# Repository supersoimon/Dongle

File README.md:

# Custom USB-C to MicroSD Dongle!
This is a custom USB Type C to MicroSD adapter capable of high-speed data transfer.

# Why I Made it :)
I've been struggling to find a USB-C to MicroSD for a Bambu Labs A1 at my school, and so I haven't been able to print on it. I found that it could be a cool project on PCB design, and a way to support my school's 3D-printing program!

# Parts
It uses a 105444 Molex USB-C plug and a 104031-0811 Molex MicroSD receptacle, connected by a GLK823 chip, with an onboard LED to show if data is transferring.

# CAD
The full CAD is available on Onshape here: https://cad.onshape.com/documents/0d5d8e7ff6d95221f6bb9616/w/a02504fd69371836af815b31/e/9594bd8276455d6ed6823f06?renderMode=0&uiState=6ab2c2f00285e009953060f3
Currently isn't going to have a case, I think it looks cooler raw.

# Images
 <br>
 <br>
 <br>
 <br>
 <br>

# BOM
| Item | Quantity | Cost (USD) | Notes |
| :--- | :---: | :---: | :--- |
| [PCB](https://cart.jlcpcb.com/shopcart/cart/) | 1 | $4.2 | |
| [PCB Shipping](https://cart.jlcpcb.com/shopcart/cart/) | 1 | $5.65 | |
| [GL823K](https://www.lcsc.com/product-detail/C284879.html) | 2 | $0.93 | |
| [Molex 105444](https://www.lcsc.com/product-detail/C134082.html) | 2 | $3.15 | |
| [Molex 104031-0811](https://www.lcsc.com/product-detail/C585350.html) | 2 | $1.67 | |
| [500mA resettable fuse](https://www.lcsc.com/product-detail/C2982262.html) | 5 | $0.39 | |
| [5.1k resistor 0805 package](https://www.lcsc.com/product-detail/C27834.html) | 100 | $0.6 | |
| [0 resistor 0805 package](https://www.lcsc.com/product-detail/C17477.html) | 100 | $0.45 | |
| [1k resistor 0805 package](https://www.lcsc.com/product-detail/C2907232.html) | 100 | $0.31 | |
| [red led 0805 package](https://www.lcsc.com/product-detail/C19171391.html) | 100 | $0.78 | |
| [0.1uF capacitor 0805 package](https://www.lcsc.com/product-detail/C49678.html) | 20 | $0.39 | |
| [1uF capacitor 0805 package](https://www.lcsc.com/product-detail/C28323.html) | 10 | $0.4 | |
| [4.7uF capacitor 0805 package](https://www.lcsc.com/product-detail/C1779.html) | 20 | $0.7 | |
| LCSC Shipping & Handling | 1 | $10.86 | |
| [Flux](https://www.amazon.ca/TOWOT-Soldering-Electronics-Pneumatic-Dispensing/dp/B0D8PRL5CP/) | 1 | $11.4 | Much of the cost is for me to start soldering these, as I've never done that before |
| [Solder Wire](https://amazon.ca/VIRALLOY®-Lead-Free-Solder-0-5mm-SAC0307/dp/B0FXX4GPWJ/) | 1 | $9.2 | |
| [ESD Tweezers](https://www.amazon.ca/Precision-ESD-Tweezers-Set-MMOBIEL/dp/B07N2QGS75/) | 1 | $7.14 | |
| [Solder Wick](https://www.amazon.ca/Solder-TOWOT-Desoldering-Wicks-SW-2530/dp/B0943PDCC4/) | 1 | $7.11 | |
| [99% IPA](https://www.amazon.ca/DELON-Isopropyl-Alcohol-Percent-Rubbing/dp/B0DD4HCV3S/) | 1 | $6.42 | |
| **Total** | **469** | **$71.75** | |fore",

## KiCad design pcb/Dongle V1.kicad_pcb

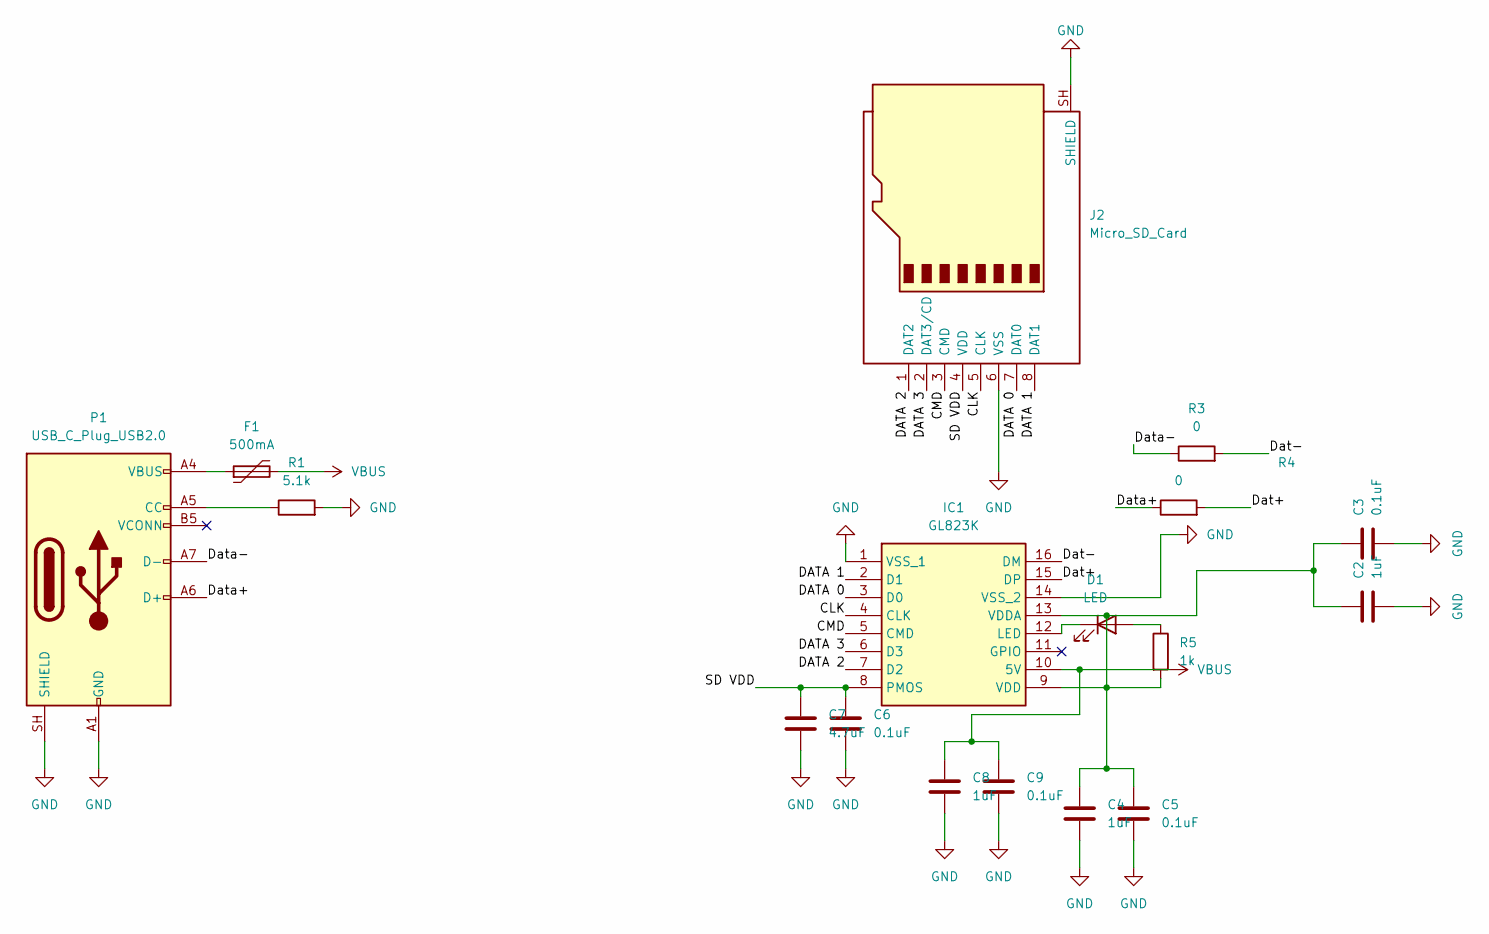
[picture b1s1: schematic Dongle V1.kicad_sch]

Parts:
C2, C4, C8: 1uF; C_0805_2012Metric_Pad1.18x1.45mm_HandSolder
C3, C5, C6, C9: 0.1uF; C_0805_2012Metric_Pad1.18x1.45mm_HandSolder
C7: 4.7uF; C_0805_2012Metric_Pad1.18x1.45mm_HandSolder
D1: LED; LED_0805_2012Metric_Pad1.15x1.40mm_HandSolder
F1: 500mA; Fuse_0805_2012Metric_Pad1.15x1.40mm_HandSolder
IC1: GL823K; SOP64P600X175-16N; Manufacturer_Part_Number GL823K
J2: Micro_SD_Card; microSD_HC_Molex_104031-0811
P1: USB_C_Plug_USB2.0; USB_C_Plug_Molex_105444
R1: 5.1k; R_0805_2012Metric_Pad1.20x1.40mm_HandSolder
R3, R4: 0; R_0805_2012Metric_Pad1.20x1.40mm_HandSolder
R5: 1k; R_0805_2012Metric_Pad1.20x1.40mm_HandSolder

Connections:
/CLK: IC1.4 (CLK), J2.5 (CLK)
/CMD: IC1.5 (CMD), J2.3 (CMD)
/DATA 0: IC1.3 (D0), J2.7 (DAT0)
/DATA 1: IC1.2 (D1), J2.8 (DAT1)
/DATA 2: IC1.7 (D2), J2.1 (DAT2)
/DATA 3: IC1.6 (D3), J2.2 (DAT3/CD)
/Dat+: IC1.15 (DP), R4.2
/Dat-: IC1.16 (DM), R3.2
/Data+: P1.A6 (D+), R4.1
/Data-: P1.A7 (D-), R3.1
/SD VDD: C6.1, C7.2, IC1.8 (PMOS), J2.4 (VDD)
GND: C2.2, C3.2, C4.2, C5.2, C6.2, C7.1, C8.2, C9.2, IC1.1 (VSS_1), IC1.14 (VSS_2), J2.6 (VSS), J2.SH (SHIELD), P1.A1 (GND), P1.A12 (GND), P1.B1 (GND), P1.B12 (GND), P1.SH (SHIELD), R1.2
unnamed: D1.2 (A), R5.1
unnamed: D1.1 (K), IC1.12 (LED)
unnamed: F1.1, P1.A4 (VBUS), P1.A9 (VBUS), P1.B4 (VBUS), P1.B9 (VBUS)
unnamed: C2.1, C3.1, C4.1, C5.1, IC1.9 (VDD), IC1.13 (VDDA), R5.2
unnamed: P1.A5 (CC), R1.1
VBUS: C8.1, C9.1, F1.2, IC1.10 (5V)

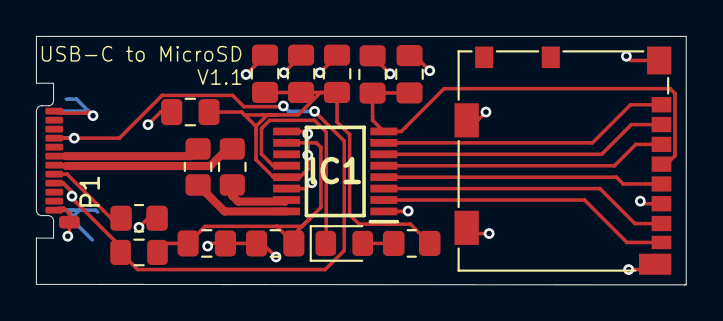
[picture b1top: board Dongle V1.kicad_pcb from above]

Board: 2 copper layers, 36.1 x 13.8 mm, 17 parts (0 on the bottom side), 18 nets.
